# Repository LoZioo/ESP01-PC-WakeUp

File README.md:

# ESP01-PC-WakeUp
Custom ESP-01 based circuit for waking up your PC remotely.

## PCB preview

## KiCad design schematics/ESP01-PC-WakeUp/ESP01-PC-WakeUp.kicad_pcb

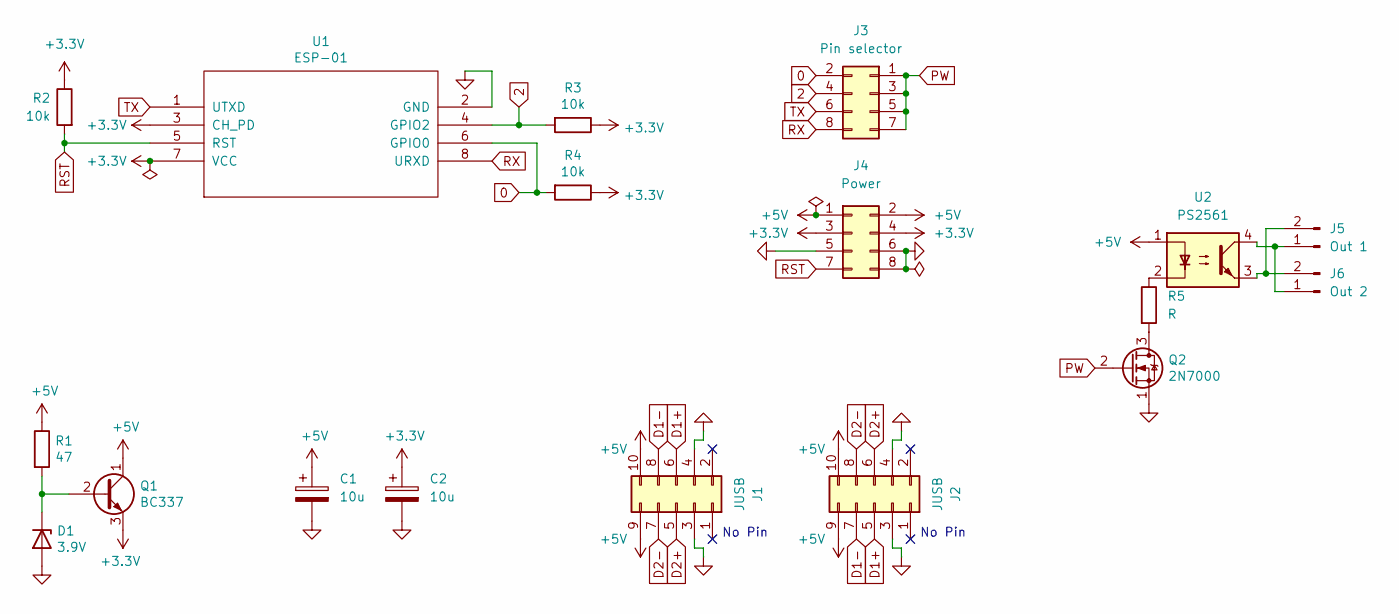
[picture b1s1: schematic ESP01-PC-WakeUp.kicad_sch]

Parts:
C1, C2: 10u; CP_Radial_D4.0mm_P1.50mm
D1: 3.9V; D_DO-41_SOD81_P7.62mm_Horizontal
J1, J2: JUSB; PinHeader_2x05_P2.54mm_Vertical
J3: Pin selector; PinHeader_2x04_P2.54mm_Vertical
J4: Power; PinHeader_2x04_P2.54mm_Vertical
J5: Out 1; PinHeader_1x02_P2.54mm_Vertical
J6: Out 2; PinHeader_1x02_P2.54mm_Vertical
Q1: BC337; TO-92_Inline
Q2: 2N7000; TO-92_Inline
R1: 47; R_Axial_DIN0207_L6.3mm_D2.5mm_P7.62mm_Horizontal
R2, R3, R4: 10k; R_Axial_DIN0207_L6.3mm_D2.5mm_P7.62mm_Horizontal
R5: R; R_Axial_DIN0207_L6.3mm_D2.5mm_P7.62mm_Horizontal
U1: ESP-01
U2: PS2561; DIP-4_W7.62mm

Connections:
0: J3.2, R4.2, U1.6 (GPIO0)
2: J3.4, R3.2, U1.4 (GPIO2)
+3V3: C2.1, J4.3, J4.4, Q1.3 (E), R2.1, R3.1, R4.1, U1.3 (CH_PD), U1.7 (VCC)
+5V: C1.1, J1.9, J1.10, J2.9, J2.10, J4.1, J4.2, Q1.1 (C), R1.1, U2.1
D1+: J1.6, J2.5
D1-: J1.8, J2.7
D2+: J1.5, J2.6
D2-: J1.7, J2.8
GND: C1.2, C2.2, D1.2 (A), J1.3, J1.4, J2.3, J2.4, J4.5, J4.6, J4.8, Q2.1 (S), U1.2 (GND)
unnamed: D1.1 (K), Q1.2 (B), R1.2
unnamed: J5.1, J6.1, U2.4
unnamed: J5.2, J6.2, U2.3
unnamed: Q2.3 (D), R5.2
unnamed: R5.1, U2.2
PW: J3.1, J3.3, J3.5, J3.7, Q2.2 (G)
RST: J4.7, R2.2, U1.5 (RST)
RX: J3.8, U1.8 (URXD)
TX: J3.6, U1.1 (UTXD)

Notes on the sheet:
No Pin

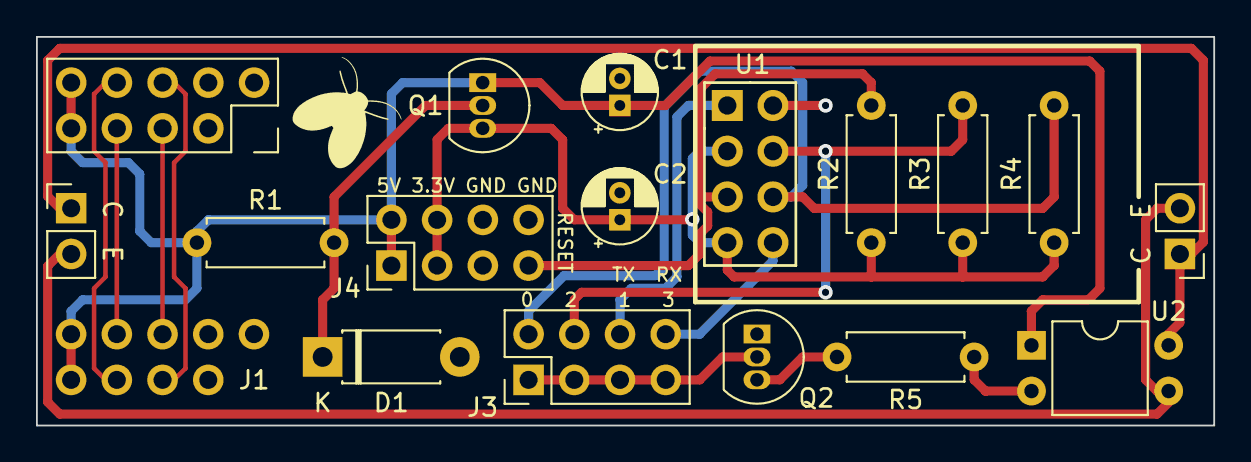
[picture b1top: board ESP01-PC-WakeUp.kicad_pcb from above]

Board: 2 copper layers, 65.4 x 21.6 mm, 18 parts (1 on the bottom side), 18 nets.

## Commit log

2023-10-26 First commit.
2023-10-27 feat: shematics and footprints
2023-10-27 feat: Out 2
2023-10-27 chore: tidying PCB.
2023-10-27 feat: first PCB release.
2023-10-27 feat(gerber)
2023-10-27 fix: added the 'JLCJLCJLCJLC' text.
2023-10-28 fix: pcb via diameters.
2023-10-28 chore
2023-10-28 docs
